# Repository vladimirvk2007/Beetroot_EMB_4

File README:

ESP32 DS18B20 Temperature Reader
https://cdn.sparkfun.com/datasheets/Sensors/Temp/DS18B20.pdf
================================

This small PlatformIO project reads temperature data from a DS18B20
one-wire temperature sensor using an ESP32 board. It uses the
OneWire and DallasTemperature libraries to request and print
temperature readings to the serial monitor every 2 seconds.

Hardware
--------
- ESP32 development board (example: YD-ESP32-S3)
- DS18B20 one-wire temperature sensor
- 4.7k Ohm pull-up resistor between Data and 3.3V

Wiring
-------
- DS18B20 Data pin -> GPIO4 on the ESP32
- DS18B20 VCC -> 3.3V
- DS18B20 GND -> GND
- 4.7k resistor between Data and 3.3V (required for reliable bus operation)

Software / Libraries
--------------------
- PlatformIO (recommended) or Arduino framework for ESP32
- Libraries used:
	- OneWire
	- DallasTemperature

Build and Upload
----------------
Use PlatformIO in VS Code or the CLI:

- Build: `pio run`
- Upload: `pio run -t upload`
- Monitor serial output: `pio device monitor -b 115200`

Usage
-----
1. Connect the hardware as described above.
2. Build and upload the firmware to your ESP32.
3. Open the serial monitor at 115200 baud to view temperature readings.

Example Output
--------------
DS18B20 Temperature Sensor Test
Found 1 sensor(s).
Requesting temperatures...DONE
Temperature for Device 1: 24.50 °C

Troubleshooting
---------------
- If no sensor is detected, check wiring and ensure the 4.7k pull-up is present.
- Verify the correct GPIO pin is used and matches `src/main.cpp` (currently GPIO4).

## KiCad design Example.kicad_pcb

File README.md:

# ESP32-S3 MQTT Demo

Демонстраційний проект для платформи **ESP32-S3**, який реалізує публікацію та прийом MQTT-повідомлень через публічний брокер HiveMQ.

Фреймворк: **ESP-IDF**

## Можливості

- Підключення до Wi-Fi та автоматичне перепідключення (до 10 спроб)
- Публікація повідомлень кожні 10 секунд із лічильником
- Прийом команд через MQTT та керування GPIO (LED)
- Віддалене керування кутом серво через MQTT
- Відповідь на запит статусу пристрою

## Апаратне забезпечення

| Компонент | Специфікація |
|-----------|-------------|
| Плата | ESP32-S3-DevKitC-1 |
| Flash | 16 MB (QIO) |
| PSRAM | 8 MB (OPI) |
| LED | GPIO 16 |
| Сигнал серво | GPIO 17 |

## Структура проєкту

```
src/
  main.cpp            — точка входу, обробка команд, публікація
lib/
  wifi/
    wifi_setup.h/.cpp — ініціалізація Wi-Fi (ESP-IDF event-driven)
  mqtt/
    mqtt.h/.cpp       — MQTT клієнт, callback API для вхідних повідомлень
  pwm/
    pwm.h/.cpp        — генерація PWM через LEDC
  servo/
    servo.h/.cpp      — керування кутом серво
  credentials/
    credentials.h     — SSID та пароль Wi-Fi
sdkconfig.defaults    — налаштування flash, PSRAM, MQTT
platformio.ini        — конфігурація PlatformIO
```

## Архітектура

MQTT модуль є незалежним транспортом — він не знає про GPIO чи бізнес-логіку. Обробка вхідних повідомлень реєструється через callback:

```c
// Реєстрація обробника до запуску клієнта
mqtt_set_message_handler(handle_mqtt_message);
mqtt_app_start();
```

## MQTT топіки

| Топік | Напрямок | Опис |
|-------|----------|------|
| `esp32s3/test` | Публікація | Повідомлення `Hello from ESP32-S3! #N` кожні 10 с |
| `esp32s3/commands` | Підписка | Вхідні команди керування |
| `esp32s3/status` | Публікація | Відповідь на `STATUS` у форматі `LED=ON;SERVO=90` |

## Обробка помилок

Помилки підключення та повторного підключення Wi-Fi виводяться в лог із кодом причини від ESP-IDF; після 10 невдалих спроб запуск MQTT припиняється. Помилки MQTT містять тип проблеми, а за наявності — TLS-, socket- або код відмови брокера. Помилки ініціалізації й публікації також містять код помилки.

### Підтримувані команди

| Команда | Дія |
|---------|-----|
| `ON` | Увімкнути LED (GPIO 16) |
| `OFF` | Вимкнути LED (GPIO 16) |
| `STATUS` | Надіслати статус на `esp32s3/status` |
| `SERVO:<кут>` | Повернути серво на кут від 0 до 180 градусів, наприклад `SERVO:90` |

Сигнальний дріт серво підключіть до GPIO 17. Для живлення серво використовуйте відповідне зовнішнє джерело, а землю джерела з'єднайте із землею ESP32.

## Налаштування

### Wi-Fi

Облікові дані зберігаються у `lib/credentials/credentials.h`:

```c
#define WIFI_SSID     "your_wifi_ssid"
#define WIFI_PASSWORD "your_wifi_password"
```

### MQTT брокер

Налаштування у `lib/mqtt/mqtt.h`:

```c
#define MQTT_BROKER_URI  "mqtt://broker.hivemq.com:1883"
```

## Збірка та прошивка

```bash
# Збірка
pio run

# Прошивка та моніторинг
pio run -t upload -t monitor
```

## Перегляд MQTT-повідомлень

**MQTT Explorer** (рекомендовано):
1. Завантажити: https://mqtt-explorer.com/
2. Підключитись до `broker.hivemq.com:1883`
3. Підписатись на топік `esp32s3/#`

**[Веб-клієнт HiveMQ](https://www.hivemq.com/demos/websocket-client/)** (без встановлення, прямо в браузері):

**Підключення:**
1. Відкрити [https://www.hivemq.com/demos/websocket-client/](https://www.hivemq.com/demos/websocket-client/)
2. Натиснути **Connect** — статус зміниться на `Connected`

**Підписка на повідомлення з ESP32-S3:**
1. У секції **Subscriptions** натиснути **Add New Topic Subscription**
2. Вписати топік `esp32s3/#` (усі повідомлення від пристрою) або `esp32s3/test`
3. Натиснути **Subscribe**
4. Нові повідомлення з'являтимуться у секції **Messages**

**Надсилання команд на ESP32-S3:**
1. У секції **Publish** вказати:
   - Topic: `esp32s3/commands`
   - Message: `ON`, `OFF`, `STATUS` або `SERVO:90`
2. Натиснути **Publish**
3. Відповідь на `STATUS` з'явиться у топіку `esp32s3/status`

**Командний рядок**:
```bash
mosquitto_sub -h broker.hivemq.com -t "esp32s3/#"
```

## Залежності

- **esp-mqtt** — вбудований компонент ESP-IDF, окремого встановлення не потребує
- **esp-wifi** — вбудований компонент ESP-IDF
- Framework: ESP-IDF
- Platform: espressif32

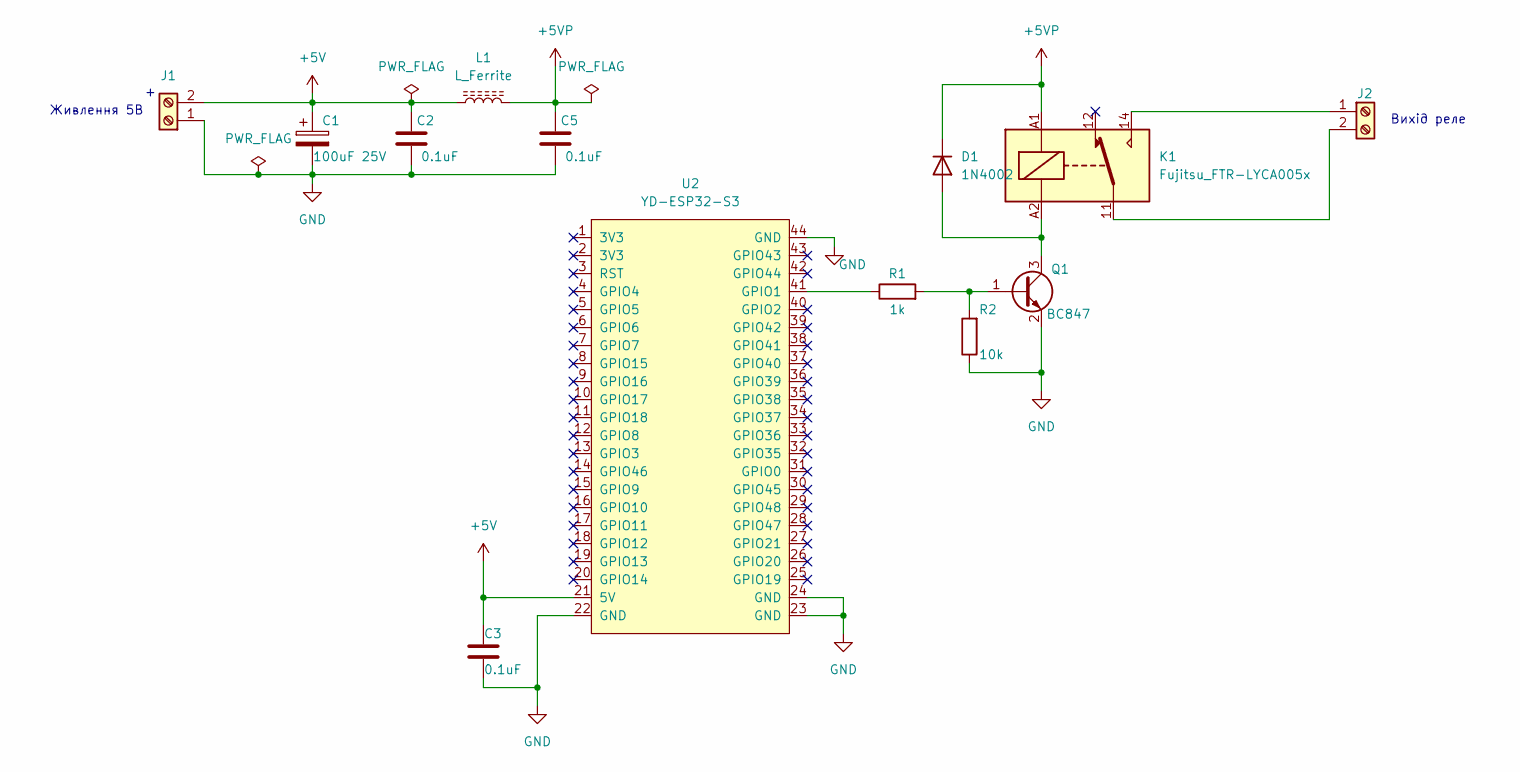
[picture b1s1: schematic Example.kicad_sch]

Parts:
C1: 100uF 25V; CP_Radial_D6.3mm_P2.50mm
C2, C3, C5: 0.1uF; C_1206_3216Metric
D1: 1N4002; D_DO-41_SOD81_P10.16mm_Horizontal
J1, J2: Screw_Terminal_01x02; TerminalBlock_Phoenix_MKDS-1,5-2-5.08_1x02_P5.08mm_Horizont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
K1: Fujitsu_FTR-LYCA005x; Relay_SPDT_Fujitsu_FTR-LYCA005x_FormC_Vertical
L1: L_Ferrite; L_2512_6332Metric_Pad1.52x3.35mm_HandSolder
Q1: BC847; SOT-23
R1: 1k; R_1206_3216Metric_Pad1.30x1.75mm_HandSolder
R2: 10k; R_1206_3216Metric
U2: YD-ESP32-S3

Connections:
+5V: C1.1, C2.1, C3.1, J1.2, L1.1, U2.21 (5V)
+5VP: C5.1, D1.1 (K), K1.A1, L1.2
GND: C1.2, C2.2, C3.2, C5.2, J1.1, Q1.2 (E), R2.1, U2.22 (GND), U2.23 (GND), U2.24 (GND), U2.44 (GND)
unnamed: D1.2 (A), K1.A2, Q1.3 (C)
unnamed: J2.1, K1.14
unnamed: J2.2, K1.11
unnamed: Q1.1 (B), R1.2, R2.2
unnamed: R1.1, U2.41 (GPIO1)

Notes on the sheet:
Вихід реле
Живлення 5В

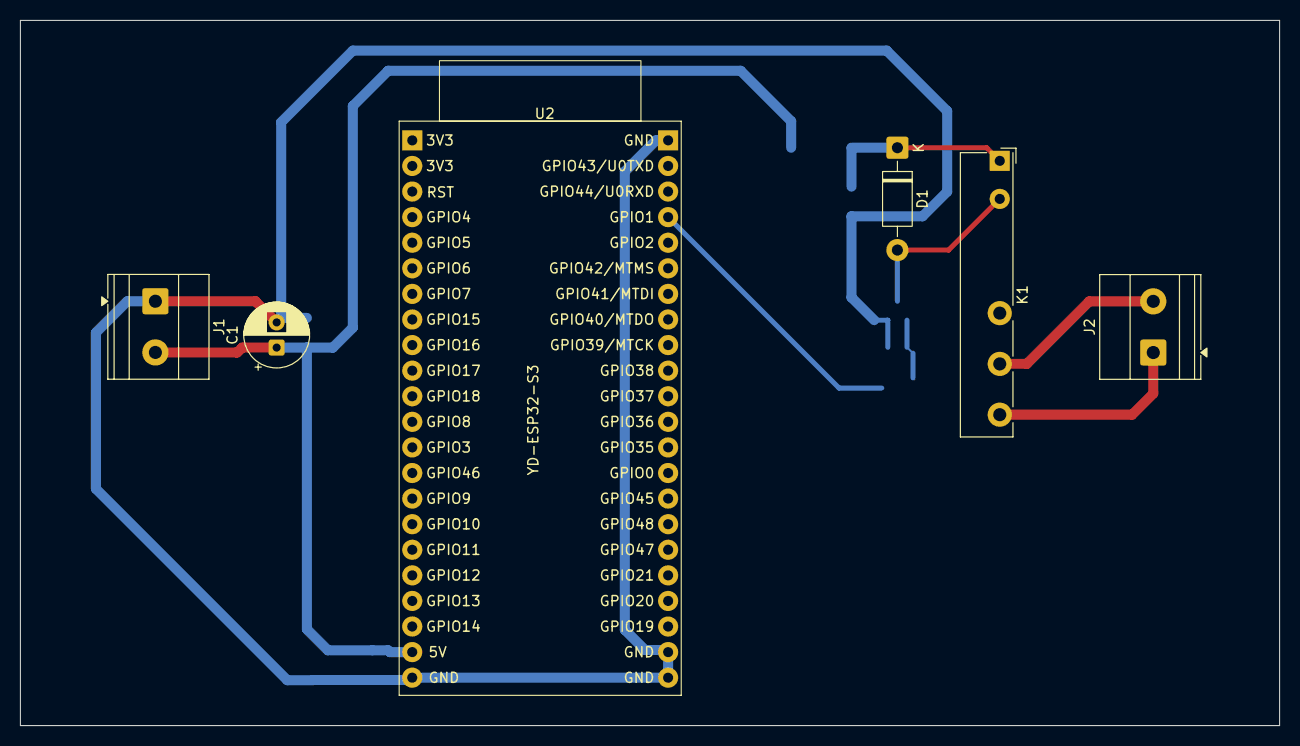
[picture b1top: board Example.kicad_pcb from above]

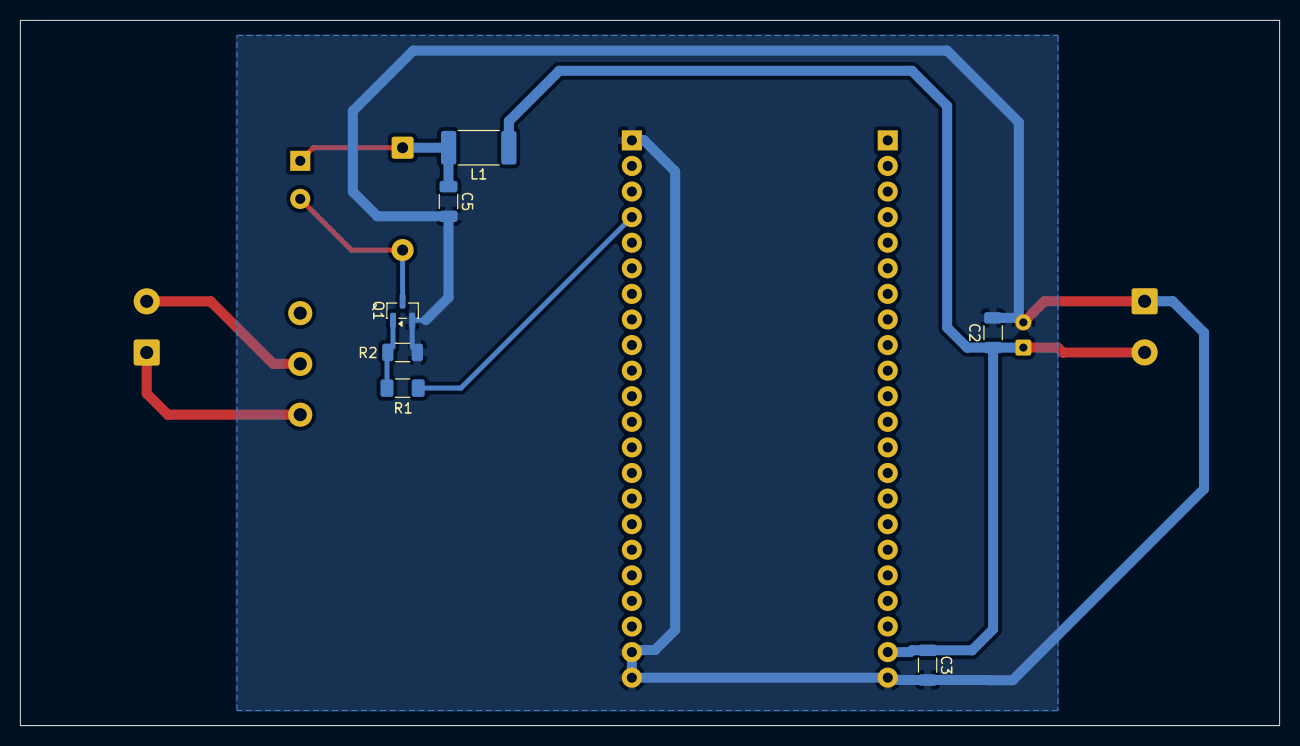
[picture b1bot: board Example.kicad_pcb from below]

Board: 2 copper layers, 125.0 x 70.0 mm, 13 parts (7 on the bottom side), 8 nets.

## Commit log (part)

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2026-02-05 Add gitignore
2026-02-05 Add initial project files
2026-02-15 Add application to reead DS18B20
2026-02-15 Udate README file
    Replace README with README.md.
    Update the contents of the README.md file.
2026-02-15 Add README description
2026-02-15 Add memory diagnostics
2026-02-15 Temp changes
2026-02-15 Resolve code style issues
2026-02-16 Fix code style issues
2026-02-19 Test
2026-02-21 Add test light control application
    ADC is used to detect light level.
2026-02-21 Add README
2026-02-21 Remove debug settings
2026-02-26 Initial commit for OTA Update
2026-02-26 Refactor and add RGB
2026-02-26 Hide credentials
2026-02-26 Add description in README
2026-03-06 Remove RGB module
2026-03-07 Motor control
2026-03-08 draft hw21
2026-03-11 Add stm32 startup
2026-03-12 Timer run and end
2026-03-12 Add timerDetachInterrupt
2026-03-12 Add start - stop timer
2026-03-12 Add README file
2026-03-13 Add FSM debounce
2026-03-14 Add FSM callback
2026-03-14 some fixes
2026-03-14 refactoring
2026-03-14 small fixes
2026-03-15 Add check FSM pointer for NULL
2026-03-15 Add .gitignore file
2026-03-15 Add STM32CubeIDE startup project
2026-03-17 Add espidf files
2026-03-17 Add memory settings
2026-03-17 Add comments
2026-03-21 Add stm32 to platformio convert prj
2026-03-21 Add compiled Prj Fix programming bug.
2026-03-21 Add GPIO_14 output
2026-03-22 Add C++ support
2026-03-24 Update README file
2026-03-27 Add ADC and README
2026-03-27 Add ADC1 measurement
2026-03-27 Add float value support
2026-03-27 Add PWM chnnel
2026-03-27 Add min function
2026-04-01 Add PWM table
2026-04-01 Add LED
2026-04-02 Servo Init
2026-04-03 Update servo
2026-04-03 Add initial code
2026-04-04 Add constants
2026-04-14 Add UART
2026-04-14 Remove unnecessary things
2026-04-14 Add UART2 initialization
2026-04-14 Add UART processing
2026-04-15 Add some minor changes
2026-04-15 Add README.md
2026-04-15 Add some changes
2026-04-15 Add README.md file
2026-04-16 Add indicator
2026-04-17 Add I2C scaner
2026-04-17 Set 115200 UART speed
2026-04-23 Some last changes
2026-04-23 Break down into modules
2026-04-24 Add DMA example
2026-04-25 Add DMA config
2026-04-25 Add DMA function
2026-04-25 Fix DMA callback
2026-04-25 Fix printf
2026-04-25 Work result
2026-04-25 Add dynamic memory allocation
2026-05-02 Add MQTT initial code
2026-05-02 Add credential
2026-05-02 Add received commands
2026-05-02 Add credentials
2026-05-02 Add WiFi settings
2026-05-02 Add MQTT functions
2026-05-02 Add LED control
2026-05-05 Add ESP-IDF implementation
2026-05-05 Fix config
2026-05-05 Some changes
2026-05-05 Add page read/write
2026-05-05 i2c test init
2026-05-05 Add separate functions
2026-05-05 Final changes
2026-05-05 Minor changes
2026-05-20 Add KiCad project
2026-05-20 Fix minor issues
2026-05-20 Removed gerbers/.gitkeep
2026-05-21 Add PID regulator schematic
2026-05-21 Some minor changes
2026-05-21 Add PID miniproject
2026-05-23 Add latest changes
2026-05-26 Add FreeRTOS example
2026-05-26 Add FreeRTOS
2026-05-28 Revert plaltformio.ini
2026-05-28 First successful build
2026-05-28 Add FreeRTOS test
2026-05-28 Remove additional script
2026-05-28 Change FreeRTOSConfig.h
2026-05-28 Move main_cpp()
2026-05-28 Minor changes in src.ios
2026-05-30 Add Queue
2026-06-04 Add FSM macro
2026-06-04 Remove unnecessury code
2026-06-04 Add mutex example
2026-06-04 Add semaphore
2026-06-06 Low sleep mode
2026-06-06 Deep Sleep
2026-06-07 Add some fixes
2026-06-07 Add some fixes and README
2026-06-07 Some minor fixes and README
2026-06-11 Initial commit for logger
2026-06-11 Add program structure diagram
2026-06-13 Add UART and Logger
2026-06-13 Add partitions table
2026-06-30 Add callbacks
2026-06-30 Add release counter
